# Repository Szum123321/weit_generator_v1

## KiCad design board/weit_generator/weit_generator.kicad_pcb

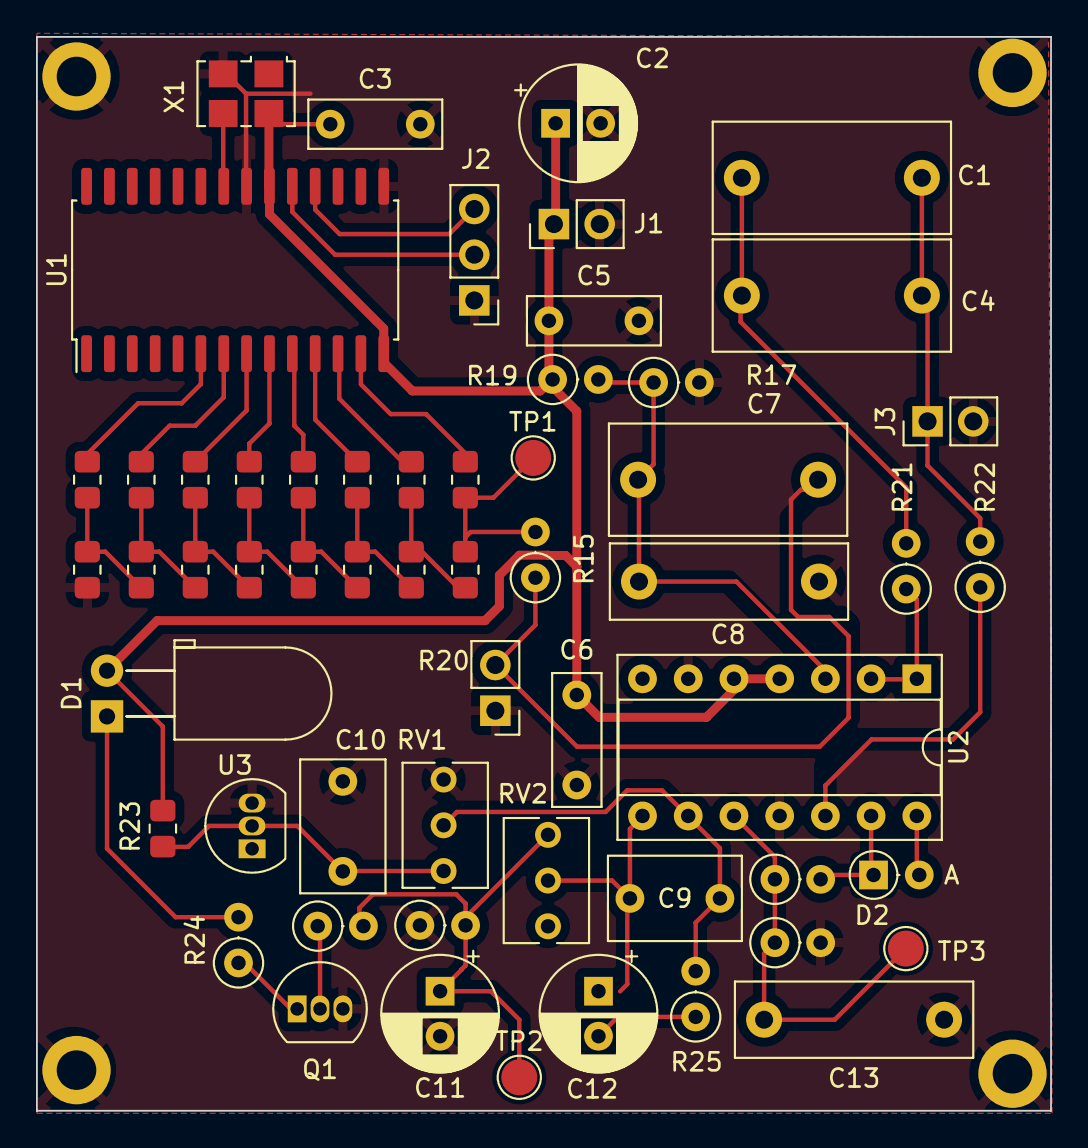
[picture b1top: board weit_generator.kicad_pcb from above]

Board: 2 copper layers, 56.3 x 59.7 mm, 57 parts (0 on the bottom side), 38 nets.

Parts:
C1, C4, C7: 100n; C_Rect_L13.0mm_W6.0mm_P10.00mm_FKS3_FKP3_MKS4
C2, C11: 100u; CP_Radial_D6.3mm_P2.50mm
C3, C5, C6: 100n; C_Rect_L7.2mm_W2.5mm_P5.00mm_FKS2_FKP2_MKS2_MKP2
C8, C13: 10n; C_Rect_L13.0mm_W4.0mm_P10.00mm_FKS3_FKP3_MKS4
C9, C10: 1u; C_Rect_L7.2mm_W4.5mm_P5.00mm_FKS2_FKP2_MKS2_MKP2
C12: 22u; CP_Radial_D6.3mm_P2.50mm
D1: LED; LED_D5.0mm_Horizontal_O3.81mm_Z3.0mm
D2: 1N6263; D_DO-35_SOD27_P2.54mm_Vertical_AnodeUp
J1: Zasilanie; PinHeader_1x02_P2.54mm_Vertical
J2: PROG; PinHeader_1x03_P2.54mm_Vertical
J3: Wyjście; PinHeader_1x02_P2.54mm_Vertical
Q1: BC547; TO-92_Inline
R1, R3, R4, R6, R9, R10, R11, R16, R18: 2k; R_0805_2012Metric_Pad1.20x1.40mm_HandSolder
R2, R5, R7, R8, R12, R13, R14, R23: 1k; R_0805_2012Metric_Pad1.20x1.40mm_HandSolder
R15: 5k; R_Axial_DIN0207_L6.3mm_D2.5mm_P2.54mm_Vertical
R17, R19: 100k; R_Axial_DIN0207_L6.3mm_D2.5mm_P2.54mm_Vertical
R20: R_Photo; PinHeader_1x02_P2.54mm_Vertical
R21, R24, R26, R28: 100; R_Axial_DIN0207_L6.3mm_D2.5mm_P2.54mm_Vertical
R22, R27, R29: 1M; R_Axial_DIN0207_L6.3mm_D2.5mm_P2.54mm_Vertical
R25: 10k; R_Axial_DIN0207_L6.3mm_D2.5mm_P2.54mm_Vertical
RV1, RV2: 10k; Potentiometer_Bourns_3266Y_Vertical
TP1, TP2, TP3: TestPoint; TestPoint_Pad_D2.0mm
U1: AVR32DA28x-xSO; SOIC-28W_7.5x17.9mm_P1.27mm
U2: MCP6004; DIP-14_W7.62mm_Socket
U3: LM4041L; TO-92_Inline
X1: SG-5032CAN; Oscillator_SMD_SeikoEpson_SG8002LB-4Pin_5.0x3.2mm

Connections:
+1V2: C10.1, R23.2, RV1.3, U3.2 (K)
+3V0: C2.1, C3.1, C5.1, C6.1, D1.2 (A), J1.1, R19.1, R23.1, U1.14 (AVDD), U1.20 (VDD), U2.4 (V+), U2.5 (+), X1.4 (VCC)
/Filtr Wyjściowy/IN: C7.1, R15.1, R20.2
/Filtr Wyjściowy/OUT: C1.1, C4.1, R21.2
/Kontrola Amplitiudy/IN: C1.2, C4.2, J3.1, R22.2
/Kontrola Amplitiudy/OUT: D1.1 (K), R24.2
/R-2R DAC/BUS0: R3.1, U1.6 (PD0)
/R-2R DAC/BUS1: R1.1, U1.7 (PD1)
/R-2R DAC/BUS2: R6.1, U1.8 (PD2)
/R-2R DAC/BUS3: R9.1, U1.9 (PD3)
/R-2R DAC/BUS4: R10.1, U1.10 (PD4)
/R-2R DAC/BUS5: R16.1, U1.11 (PD5)
/R-2R DAC/BUS6: R18.1, U1.12 (PD6)
/R-2R DAC/BUS7: R11.1, U1.13 (VREFA/PD7)
/R-2R DAC/OUT: R11.2, R14.1, R15.2, TP1.1
GND: C2.2, C3.2, C5.2, C6.2, C8.1, C10.2, C11.2, C13.1, J1.2, J2.1, J3.2, Q1.3 (E), R4.2, R17.2, R20.1, R27.1, R29.2, RV1.1, U1.15 (GND), U1.21 (GND), U2.6 (-), U2.11 (V-), U3.3 (A), X1.2 (GND)
unnamed: C11.1, R26.2, R27.2, RV2.3, TP2.1
unnamed: C9.2, C12.1, RV2.2, U2.8
unnamed: C12.2, R25.1
unnamed: D2.2 (A), U2.14
unnamed: D2.1 (K), R28.2, U2.13 (-)
unnamed: J2.2, U1.19 (UPDI)
unnamed: J2.3, U1.18 (~RESET/PF6)
unnamed: Q1.2 (B), R26.1
unnamed: Q1.1 (C), R24.1
unnamed: R1.2, R2.2, R8.1
unnamed: R2.1, R5.2, R6.2
unnamed: R3.2, R4.1, R8.2
unnamed: R5.1, R7.2, R9.2
unnamed: R7.1, R10.2, R13.2
unnamed: R12.1, R14.2, R18.2
unnamed: R12.2, R13.1, R16.2
unnamed: U1.22 (PA0), X1.3 (OUT)
unnamed: C7.2, C8.2, R17.1, R19.2, U2.3 (+)
unnamed: R21.1, U2.1, U2.2 (-)
unnamed: C13.2, R28.1, R29.1, TP3.1, U2.10 (+)
unnamed: C9.1, R25.2, RV1.2, U2.9 (-)
unnamed: R22.1, U2.12 (+)

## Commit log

2023-03-28 init
2023-04-10 eveythning compiles now
2023-04-11 implementation details, spellcheck
2023-04-12 Repaired PDF, compressed images
2023-04-12 XD pomyliłem kolejność rejestrów
2023-04-13 added filtering
2023-04-14 hopefully repaired instability
2023-04-14 moved around files
2023-04-14 New layout
2023-04-15 finished board, added test desription and tuning to docs
2023-04-15 added fancy graphics
2023-04-15 kończę raport techniczny
2023-04-15 WIELKA POLONIAAAAA
2023-04-15 potężny polski assembler
2023-04-15 Final revision - submitting
2023-04-15 Last minute poprawki
2023-05-06 changed OR to ORI
